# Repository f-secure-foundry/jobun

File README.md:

Introduction
============

jobun | https://github.com/f-secure-foundry/jobun  
Copyright (c) F-Secure Corporation

The jobun (序文) board implements a platform for transmission of truly
arbitrary Ethernet (802.3u - 100BASE-FX, 100BASETX and 10BASE-Te) packets, by
means of an FPGA based software Media Access Control (MAC) connected to a
physical (PHY) Ethernet transceiver.

The FPGA is a Lattice Semiconductor MachXO2 (P/N LCMXO2-1200HC-4SG32C), the
Ethernet transceiver is a Texas Instruments DP83822.

The PCB features a design that allows to use the FPGA side of the board
independently of the Ethernet PHY one. A 2.54mm 20x2 pin header must be
soldered to interconnect the two sides through connection shunts (jumpers).

With some courage, the two sides can also be snapped off each other for fully
independent use.

The board features a USB micro-AB receptacle for programming and operation.

The jobun design has been initially designed to provide a platform for the
Start-of-Frame delimiter (SFD) manipulation attacks described in the following
research:

* A. Barisani and D. Bianco
  “Fully Arbitrary 802.3 Packet Injection: Maximizing the Ethernet Attack Surface”  
  [Link](https://github.com/abarisani/abarisani.github.io/tree/master/research/802.3)

Authors
=======

Andrea Barisani  
andrea@inversepath.com  

Andrej Rosano  
andrej@inversepath.com  

Firmware
========

The on-board MachXO2 FPGA can be programmed, over USB, by placing a jumper on
the JP1 connector located on the upper left corner. The jumper must be then
removed and the board restarted to allow Ethernet PHY reconfiguration and
firmware startup.

The `firmware` directory contains a Lattice Diamond project file for a basic
packet transmission tool named file2cable to honour FX's homonym tool, part of
the legendary IRPAS from Phenoelit.

While the original IRPAS file2cable tool can be used to transmit a "MAC Frame",
jobun can send a "MAC Packet" (see paper linked earlier), therefore achieving
better coverage ;) in transmitting an actual file to the cable. The file in
question is `firmware/mac_pkt.txt`.

This [wiki](https://wiki.archlinux.org/index.php/Lattice_Diamond) contains
useful information on how to get started with Lattice Diamond.

Revision information
====================

Current schematics and layout files have been designed in KiCad 5.0.1.

PCB information
===============

2 layers, 1.60mm thickness, top only components  
Outer layers 0.5 oz base copper foil  
Inner layers   1 oz base copper foil  
width (X) 55.1 mm, height (Y) 50.5 mm  
Blue soldermask, white component legend

DRC information
---------------

Minimum track width:            0.254 mm  
Minimum via diameter:           0.450 mm  
Outer layer track width:        0.139 mm  
Outer layer isolation distance: 0.127 mm  
Outer layer annular ring:       0.100 mm  
Smallest final hole (plated):   0.150 mm

License
=======

Copyright (c) F-Secure Corporation

This is an open hardware design licensed under the terms of the CERN Open
Hardware Licence (OHL) v1.2.

You may redistribute and modify this documentation under the terms of the CERN
OHL v.1.2 (http://ohwr.org/cernohl). This documentation is distributed WITHOUT
ANY EXPRESS OR IMPLIED WARRANTY, INCLUDING OF MERCHANTABILITY, SATISFACTORY
QUALITY AND FITNESS FOR A PARTICULAR PURPOSE. Please see the CERN OHL v.1.2 for
applicable conditions.

The following exceptions apply:

- `hardware/lib.snapeda`: all files in this directory are imported or modified
  from SnapEDA symbols and footprints, therefore the license at
  https://www.snapeda.com/about/FAQ/#license applies.

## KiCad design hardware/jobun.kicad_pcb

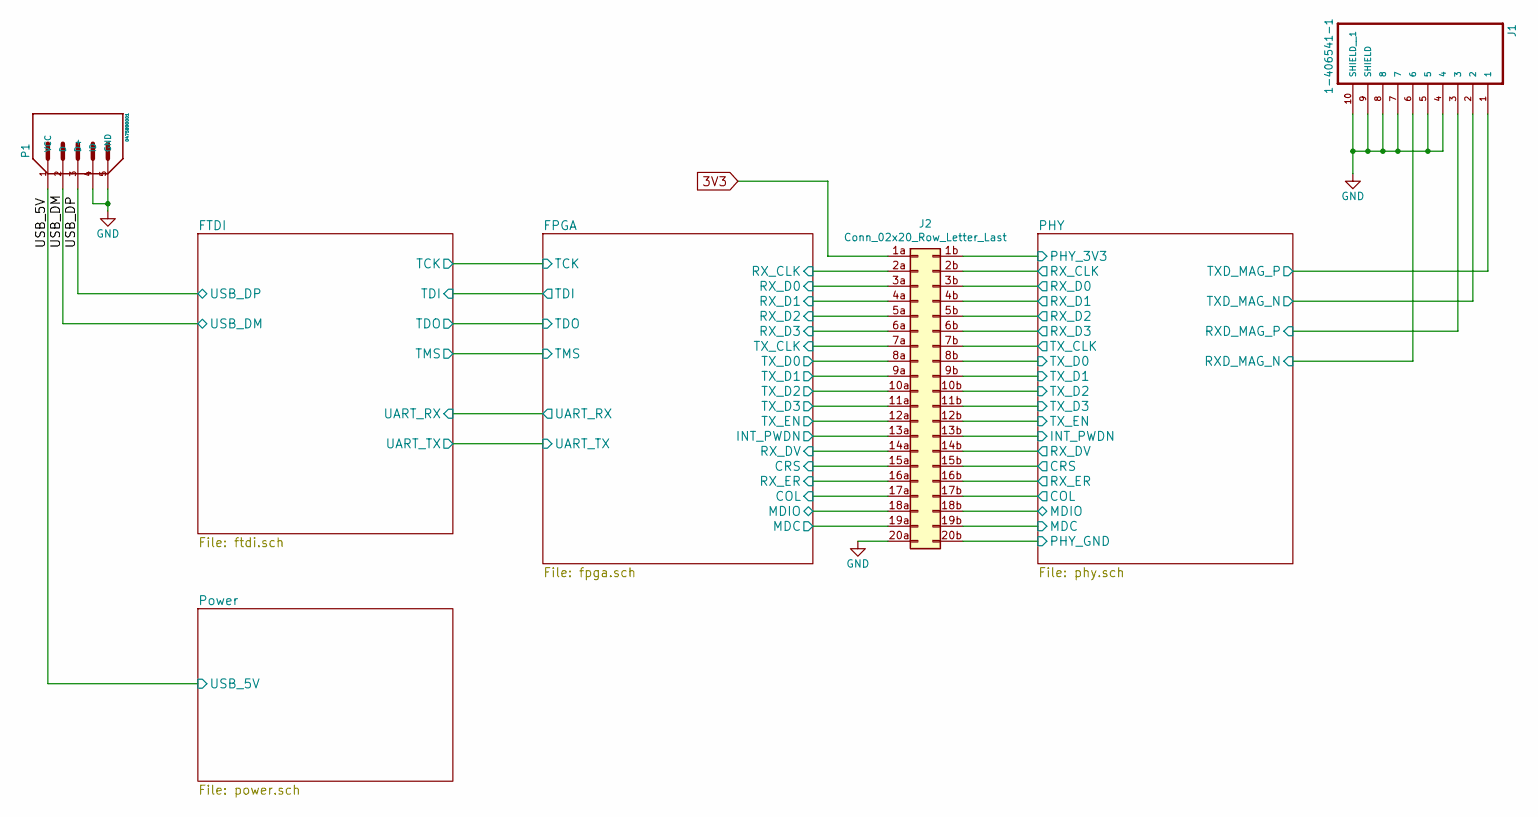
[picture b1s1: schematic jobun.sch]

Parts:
J1: 1-406541-1; CONN_1-406541-1; Mfg PN 1-406541-1
J2: Conn_02x20_Row_Letter_Last; jobun_pcb_mezzanine-20X2
P1: 0475890001; MOLEX_0475890001; Mfg PN 0475890001

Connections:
3V3: J2.1a; also elsewhere on the board
/FPGA/COL: J2.17a; also elsewhere on the board
/FPGA/CRS: J2.15a; also elsewhere on the board
/FPGA/INT_PWDN: J2.13a; also elsewhere on the board
/FPGA/MDC: J2.19a; also elsewhere on the board
/FPGA/MDIO: J2.18a; also elsewhere on the board
/FPGA/RX_CLK: J2.2a; also elsewhere on the board
/FPGA/RX_D0: J2.3a; also elsewhere on the board
/FPGA/RX_D1: J2.4a; also elsewhere on the board
/FPGA/RX_D2: J2.5a; also elsewhere on the board
/FPGA/RX_D3: J2.6a; also elsewhere on the board
/FPGA/RX_DV: J2.14a; also elsewhere on the board
/FPGA/RX_ER: J2.16a; also elsewhere on the board
/FPGA/TX_CLK: J2.7a; also elsewhere on the board
/FPGA/TX_D0: J2.8a; also elsewhere on the board
/FPGA/TX_D1: J2.9a; also elsewhere on the board
/FPGA/TX_D2: J2.10a; also elsewhere on the board
/FPGA/TX_D3: J2.11a; also elsewhere on the board
/FPGA/TX_EN: J2.12a; also elsewhere on the board
/PHY/COL: J2.17b; also elsewhere on the board
/PHY/CRS: J2.15b; also elsewhere on the board
/PHY/INT_PWDN: J2.13b; also elsewhere on the board
/PHY/MDC: J2.19b; also elsewhere on the board
/PHY/MDIO: J2.18b; also elsewhere on the board
/PHY/PHY_3V3: J2.1b; also elsewhere on the board
/PHY/RXD_MAG_N: J1.6; also elsewhere on the board
/PHY/RXD_MAG_P: J1.3; also elsewhere on the board
/PHY/RX_CLK: J2.2b; also elsewhere on the board
/PHY/RX_D0: J2.3b; also elsewhere on the board
/PHY/RX_D1: J2.4b; also elsewhere on the board
/PHY/RX_D2: J2.5b; also elsewhere on the board
/PHY/RX_D3: J2.6b; also elsewhere on the board
/PHY/RX_DV: J2.14b; also elsewhere on the board
/PHY/RX_ER: J2.16b; also elsewhere on the board
/PHY/TXD_MAG_N: J1.2; also elsewhere on the board
/PHY/TXD_MAG_P: J1.1; also elsewhere on the board
/PHY/TX_CLK: J2.7b; also elsewhere on the board
/PHY/TX_D0: J2.8b; also elsewhere on the board
/PHY/TX_D1: J2.9b; also elsewhere on the board
/PHY/TX_D2: J2.10b; also elsewhere on the board
/PHY/TX_D3: J2.11b; also elsewhere on the board
/PHY/TX_EN: J2.12b; also elsewhere on the board
/USB_5V: P1.1 (VCC); also elsewhere on the board
/USB_DM: P1.2 (D); also elsewhere on the board
/USB_DP: P1.3 (D+); also elsewhere on the board
GND: J1.4, J1.5, J1.7, J1.8, J1.9 (SHIELD), J1.10 (SHIELD__1), J2.20a, J2.20b, P1.4 (ID), P1.5 (GND); also elsewhere on the board

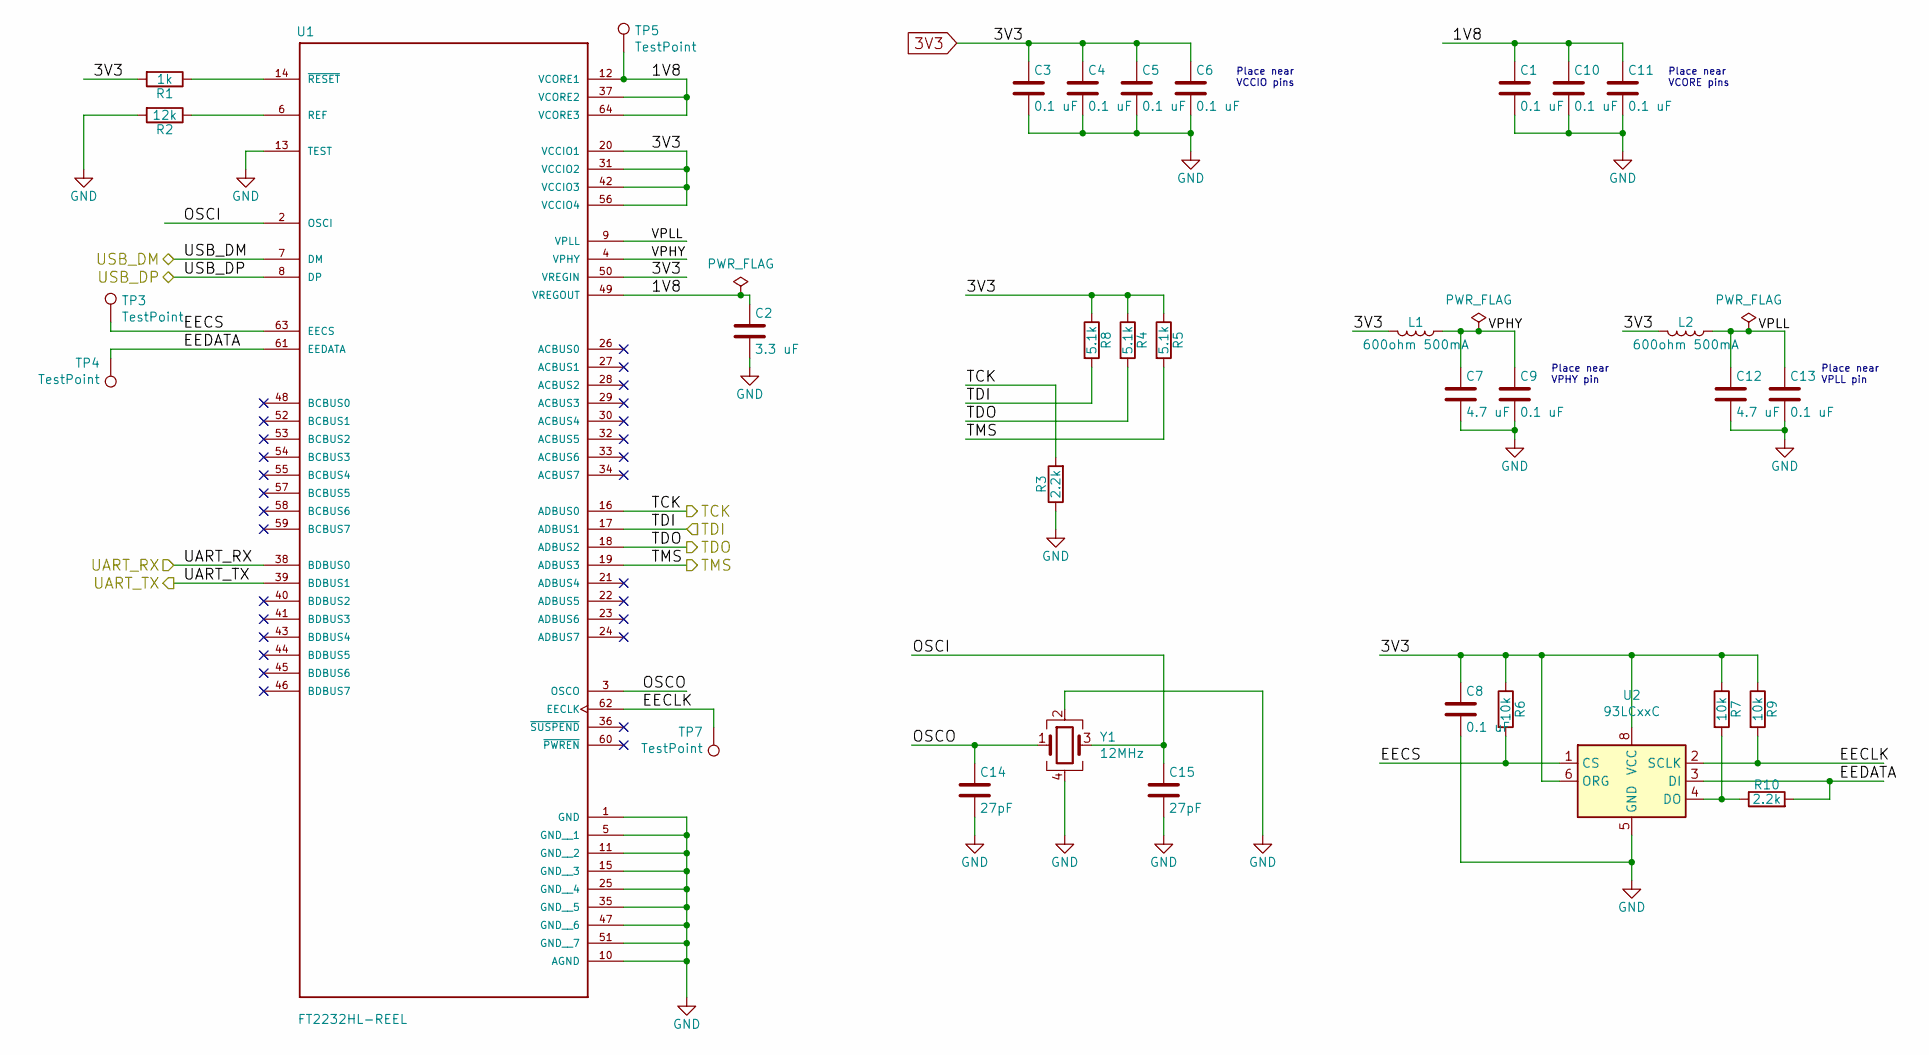
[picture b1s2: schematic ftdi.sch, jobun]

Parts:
C1, C3, C4, C5, C6, C8, C9, C10, C11, C13: 0.1 uF; SM0603; Mfg PN C1608X7R1E104K080AA
C2: 3.3 uF; SM0603; Mfg PN C1608X5R1C335K080AC
C7, C12: 4.7 uF; SM0603; Mfg PN CGB3B1X5R1A475M055AC
C14, C15: 27pF; SM0603; Mfg PN GRM1885C1H270FA01D
L1, L2: 600ohm 500mA; SM0603; Mfg PN BLM18AG601SN1D
R1: 1k; SM0603; Mfg PN RCA06031K00FKEAHP
R2: 12k; SM0603; Mfg PN CRCW060312K0FKEAC
R3, R10: 2.2k; SM0603; Mfg PN RCS06032K20JNEA
R4, R5, R8: 5.1k; SM0603; Mfg PN CRCW06035K10FKEAC
R6, R7, R9: 10k; SM0603; Mfg PN CRCW060310K0FKEA
TP3, TP4, TP5, TP7: TestPoint; TP
U1: FT2232HL-REEL; QFP50P1200X1200X160-64N; Mfg PN FT2232HL-REEL
U2: 93LCxxC; 8L_SOIC_Narrow_3_90_SN_C04-057C; Mfg PN 93LC56C-I/SN
Y1: 12MHz; TXC-3.2x2.5; Mfg PN 7M-12.000MAAJ-T

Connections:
3V3: C3.1, C4.1, C5.1, C6.1, C8.1, L1.1, L2.1, R1.2, R4.1, R5.1, R6.1, R7.1, R8.1, R9.1, U1.20 (VCCIO1), U1.31 (VCCIO2), U1.42 (VCCIO3), U1.50 (VREGIN), U1.56 (VCCIO4), U2.6 (ORG), U2.8 (VCC); also elsewhere on the board
/FPGA/TCK: R3.2, U1.16 (ADBUS0); also elsewhere on the board
/FPGA/TDI: R8.2, U1.17 (ADBUS1); also elsewhere on the board
/FPGA/TDO: R4.2, U1.18 (ADBUS2); also elsewhere on the board
/FPGA/TMS: R5.2, U1.19 (ADBUS3); also elsewhere on the board
/FPGA/UART_RX: U1.38 (BDBUS0); also elsewhere on the board
/FPGA/UART_TX: U1.39 (BDBUS1); also elsewhere on the board
/FTDI/1V8: C1.1, C2.1, C10.1, C11.1, TP5.1, U1.12 (VCORE1), U1.37 (VCORE2), U1.49 (VREGOUT), U1.64 (VCORE3)
/FTDI/EECLK: R9.2, TP7.1, U1.62 (EECLK), U2.2 (SCLK)
/FTDI/EECS: R6.2, TP3.1, U1.63 (EECS), U2.1 (CS)
/FTDI/EEDATA: R10.2, TP4.1, U1.61 (EEDATA), U2.3 (DI)
/FTDI/OSCI: C15.1, U1.2 (OSCI), Y1.3
/FTDI/OSCO: C14.1, U1.3 (OSCO), Y1.1
/FTDI/VPHY: C7.1, C9.1, L1.2, U1.4 (VPHY)
/FTDI/VPLL: C12.1, C13.1, L2.2, U1.9 (VPLL)
/USB_DM: U1.7 (DM); also elsewhere on the board
/USB_DP: U1.8 (DP); also elsewhere on the board
GND: C1.2, C2.2, C3.2, C4.2, C5.2, C6.2, C7.2, C8.2, C9.2, C10.2, C11.2, C12.2, C13.2, C14.2, C15.2, R2.2, R3.1, U1.1 (GND), U1.5 (GND__1), U1.10 (AGND), U1.11 (GND__2), U1.13 (TEST), U1.15 (GND__3), U1.25 (GND__4), U1.35 (GND__5), U1.47 (GND__6), U1.51 (GND__7), U2.5 (GND), Y1.2, Y1.4; also elsewhere on the board
unnamed: R1.1, U1.14 (~RESET~)
unnamed: R2.1, U1.6 (REF)
unnamed: R7.2, R10.1, U2.4 (DO)

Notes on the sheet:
Place near VCORE pins
Place near VCCIO pins
Place near VPLL pin
Place near VPHY pin

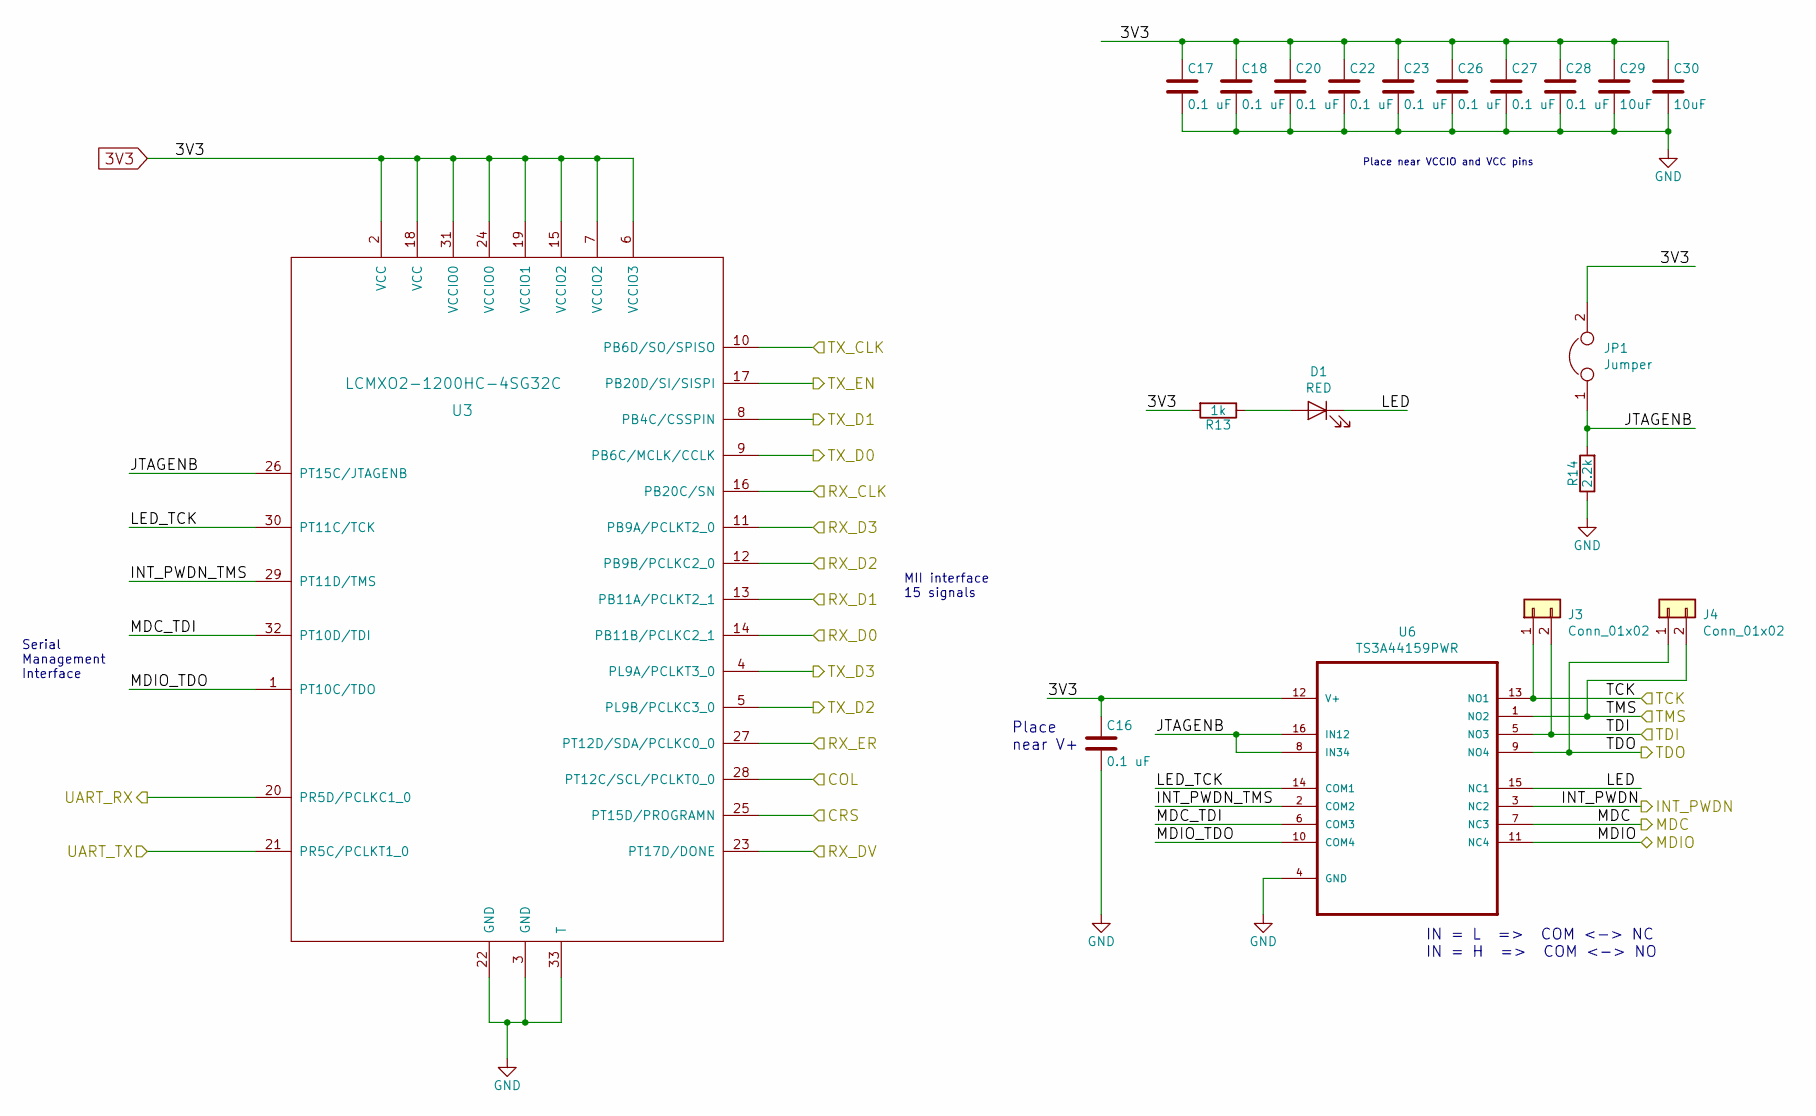
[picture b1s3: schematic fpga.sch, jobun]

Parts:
C16, C17, C18, C20, C22, C23, C26, C27, C28: 0.1 uF; SM0603; Mfg PN C1608X7R1E104K080AA
C29, C30: 10uF; SM0603; Mfg PN C1608X5R1A106M080AC
D1: RED; SM0603; Mfg PN LTST-C190KRKT
J3, J4: Conn_01x02; pinhead-1X2
JP1: Jumper; pinhead-1X2
R13: 1k; SM0603; Mfg PN RCA06031K00FKEAHP
R14: 2.2k; SM0603; Mfg PN RCS06032K20JNEA
U3: LCMXO2-1200HC-4SG32C; SG32C; Mfg PN LCMXO2-1200HC-4SG32C
U6: TS3A44159PWR; Mfg PN TS3A44159PWR

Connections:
3V3: C16.1, C17.1, C18.1, C20.1, C22.1, C23.1, C26.1, C27.1, C28.1, C29.1, C30.1, JP1.2, R13.2, U3.2 (VCC), U3.6 (VCCIO3), U3.7 (VCCIO2), U3.15 (VCCIO2), U3.18 (VCC), U3.19 (VCCIO1), U3.24 (VCCIO0), U3.31 (VCCIO0), U6.12 (V+); also elsewhere on the board
/FPGA/COL: U3.28 (PT12C/SCL/PCLKT0_0); also elsewhere on the board
/FPGA/CRS: U3.25 (PT15D/PROGRAMN); also elsewhere on the board
/FPGA/INT_PWDN: U6.3 (NC2); also elsewhere on the board
/FPGA/INT_PWDN_TMS: U3.29 (PT11D/TMS), U6.2 (COM2)
/FPGA/JTAGENB: JP1.1, R14.2, U3.26 (PT15C/JTAGENB), U6.8 (IN34), U6.16 (IN12)
/FPGA/LED: D1.1 (K), U6.15 (NC1)
/FPGA/LED_TCK: U3.30 (PT11C/TCK), U6.14 (COM1)
/FPGA/MDC: U6.7 (NC3); also elsewhere on the board
/FPGA/MDC_TDI: U3.32 (PT10D/TDI), U6.6 (COM3)
/FPGA/MDIO: U6.11 (NC4); also elsewhere on the board
/FPGA/MDIO_TDO: U3.1 (PT10C/TDO), U6.10 (COM4)
/FPGA/RX_CLK: U3.16 (PB20C/SN); also elsewhere on the board
/FPGA/RX_D0: U3.14 (PB11B/PCLKC2_1); also elsewhere on the board
/FPGA/RX_D1: U3.13 (PB11A/PCLKT2_1); also elsewhere on the board
/FPGA/RX_D2: U3.12 (PB9B/PCLKC2_0); also elsewhere on the board
/FPGA/RX_D3: U3.11 (PB9A/PCLKT2_0); also elsewhere on the board
/FPGA/RX_DV: U3.23 (PT17D/DONE); also elsewhere on the board
/FPGA/RX_ER: U3.27 (PT12D/SDA/PCLKC0_0); also elsewhere on the board
/FPGA/TCK: J3.1, U6.13 (NO1); also elsewhere on the board
/FPGA/TDI: J3.2, U6.5 (NO3); also elsewhere on the board
/FPGA/TDO: J4.1, U6.9 (NO4); also elsewhere on the board
/FPGA/TMS: J4.2, U6.1 (NO2); also elsewhere on the board
/FPGA/TX_CLK: U3.10 (PB6D/SO/SPISO); also elsewhere on the board
/FPGA/TX_D0: U3.9 (PB6C/MCLK/CCLK); also elsewhere on the board
/FPGA/TX_D1: U3.8 (PB4C/CSSPIN); also elsewhere on the board
/FPGA/TX_D2: U3.5 (PL9B/PCLKC3_0); also elsewhere on the board
/FPGA/TX_D3: U3.4 (PL9A/PCLKT3_0); also elsewhere on the board
/FPGA/TX_EN: U3.17 (PB20D/SI/SISPI); also elsewhere on the board
/FPGA/UART_RX: U3.20 (PR5D/PCLKC1_0); also elsewhere on the board
/FPGA/UART_TX: U3.21 (PR5C/PCLKT1_0); also elsewhere on the board
GND: C16.2, C17.2, C18.2, C20.2, C22.2, C23.2, C26.2, C27.2, C28.2, C29.2, C30.2, R14.1, U3.3 (GND), U3.22 (GND), U3.33 (T), U6.4 (GND); also elsewhere on the board
unnamed: D1.2 (A), R13.1

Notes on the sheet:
Place near VCCIO and VCC pins
MII interface 15 signals
Serial Management Interface
IN = L => COM <-> NC IN = H => COM <-> NO
Place near V+

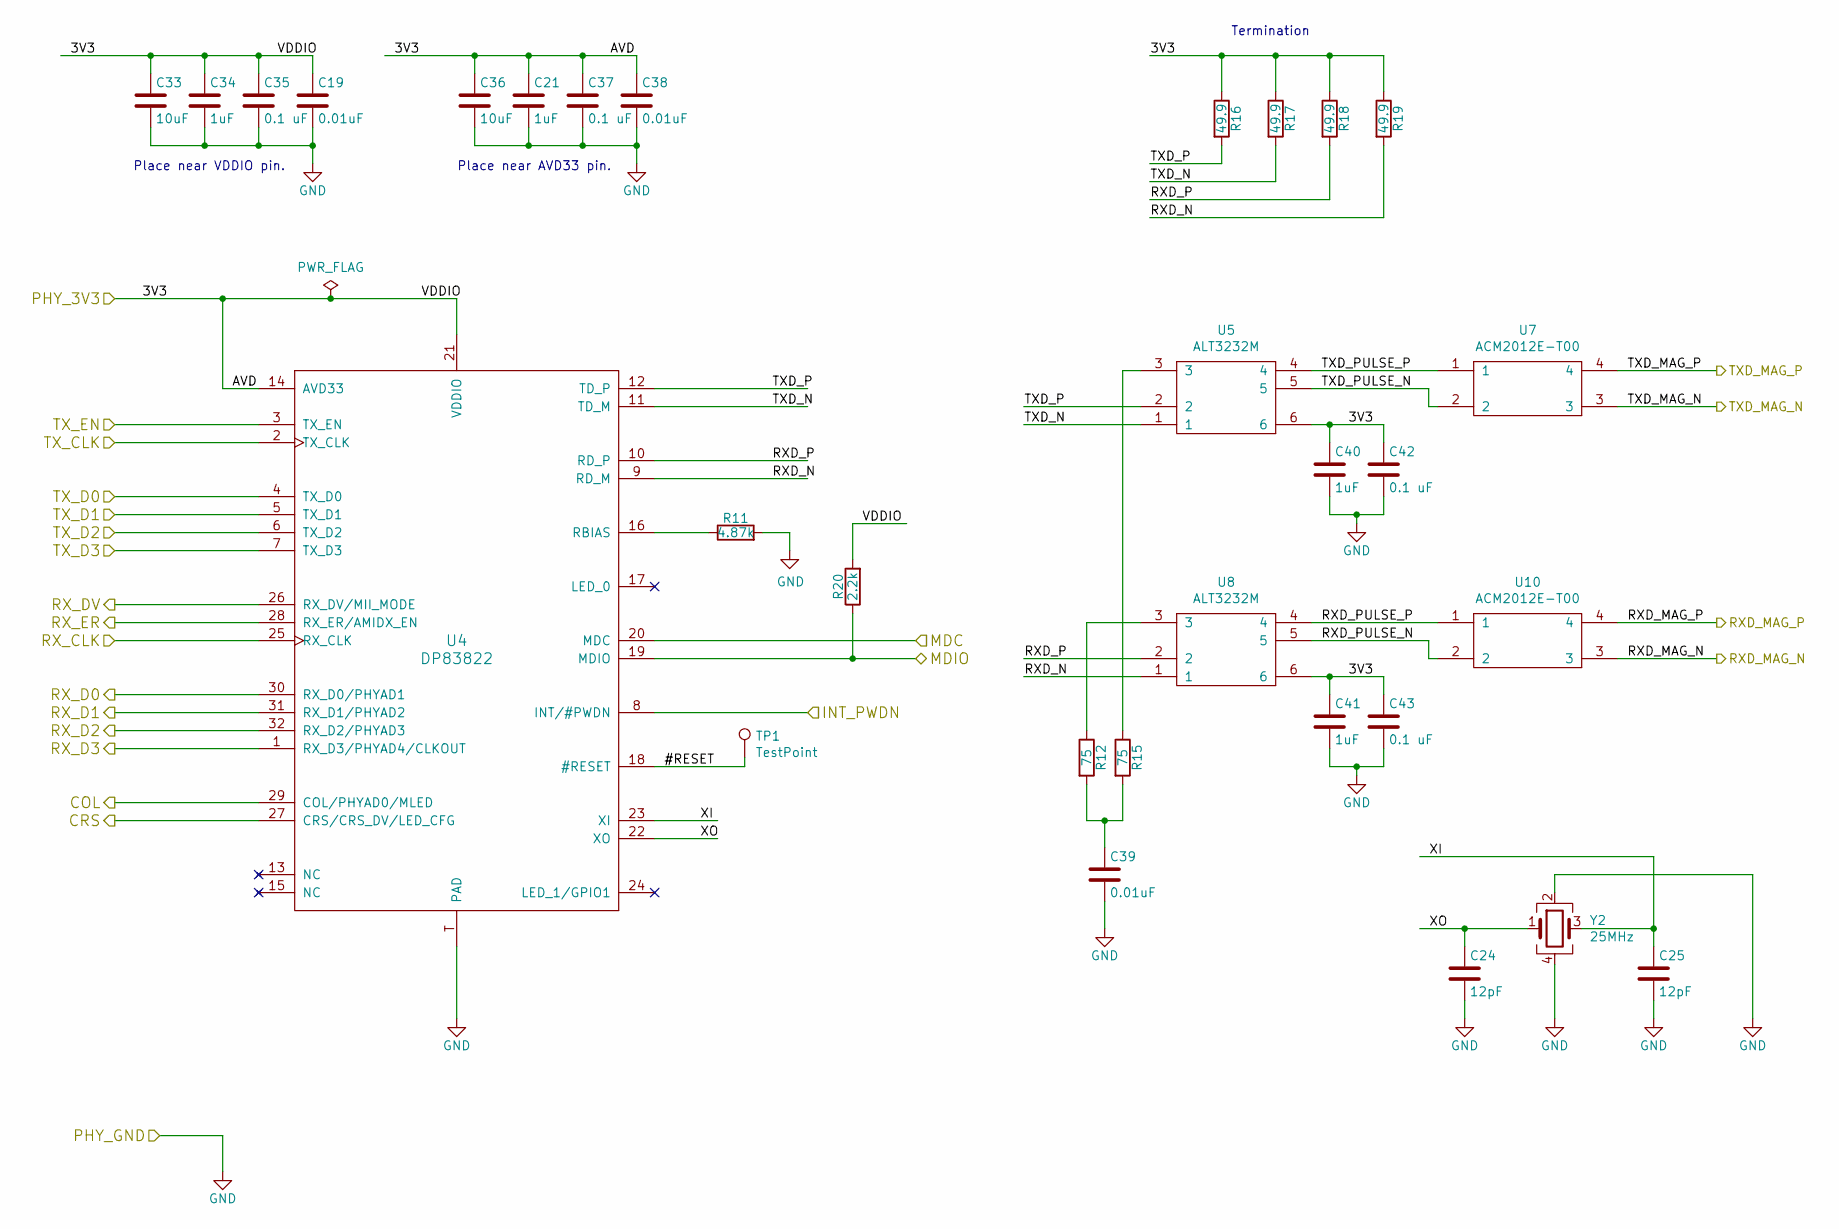
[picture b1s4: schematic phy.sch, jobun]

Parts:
C19, C38, C39: 0.01uF; SM0603; Mfg PN CGA3E2X7R2A103K080AA
C21, C34, C40, C41: 1uF; SM0603; Mfg PN CGA3E1X7R1C105M080AC
C24, C25: 12pF; SM0603; Mfg PN C1608NP02A120J080AA
C33, C36: 10uF; SM0603; Mfg PN C1608X5R1A106M080AC
C35, C37, C42, C43: 0.1 uF; SM0603; Mfg PN C1608X7R1E104K080AA
R11: 4.87k; SM0603; Mfg PN CRCW06034K87FKEA
R12, R15: 75; SM0603; Mfg PN RCS060375R0FKEA
R16, R17, R18, R19: 49.9; SM0603; Mfg PN CRCW060349R9FKEAHP
R20: 2.2k; SM0603; Mfg PN RCS06032K20JNEA
TP1: TestPoint; TP
U4: DP83822; VQFN-32; Mfg PN DP83822IFRHBT
U5, U8: ALT3232M; Mfg PN ALT3232M-151-T001
U7, U10: ACM2012E-T00; Mfg PN ACM2012E-900-2P-T00
Y2: 25MHz; OSCCC250X320X70-4N; Mfg PN ABM8AIG-25.000MHZ-12-2Z-T3

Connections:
/PHY/#RESET: TP1.1, U4.18 (#RESET)
/PHY/COL: U4.29 (COL/PHYAD0/MLED); also elsewhere on the board
/PHY/CRS: U4.27 (CRS/CRS_DV/LED_CFG); also elsewhere on the board
/PHY/INT_PWDN: U4.8 (INT/#PWDN); also elsewhere on the board
/PHY/MDC: U4.20 (MDC); also elsewhere on the board
/PHY/MDIO: R20.1, U4.19 (MDIO); also elsewhere on the board
/PHY/PHY_3V3: C19.1, C21.1, C33.1, C34.1, C35.1, C36.1, C37.1, C38.1, C40.1, C41.1, C42.1, C43.1, R16.1, R17.1, R18.1, R19.1, R20.2, U4.14 (AVD33), U4.21 (VDDIO), U5.6, U8.6; also elsewhere on the board
/PHY/RXD_MAG_N: U10.3; also elsewhere on the board
/PHY/RXD_MAG_P: U10.4; also elsewhere on the board
/PHY/RXD_N: R19.2, U4.9 (RD_M), U8.1
/PHY/RXD_P: R18.2, U4.10 (RD_P), U8.2
/PHY/RXD_PULSE_N: U8.5, U10.2
/PHY/RXD_PULSE_P: U8.4, U10.1
/PHY/RX_CLK: U4.25 (RX_CLK); also elsewhere on the board
/PHY/RX_D0: U4.30 (RX_D0/PHYAD1); also elsewhere on the board
/PHY/RX_D1: U4.31 (RX_D1/PHYAD2); also elsewhere on the board
/PHY/RX_D2: U4.32 (RX_D2/PHYAD3); also elsewhere on the board
/PHY/RX_D3: U4.1 (RX_D3/PHYAD4/CLKOUT); also elsewhere on the board
/PHY/RX_DV: U4.26 (RX_DV/MII_MODE); also elsewhere on the board
/PHY/RX_ER: U4.28 (RX_ER/AMIDX_EN); also elsewhere on the board
/PHY/TXD_MAG_N: U7.3; also elsewhere on the board
/PHY/TXD_MAG_P: U7.4; also elsewhere on the board
/PHY/TXD_N: R17.2, U4.11 (TD_M), U5.1
/PHY/TXD_P: R16.2, U4.12 (TD_P), U5.2
/PHY/TXD_PULSE_N: U5.5, U7.2
/PHY/TXD_PULSE_P: U5.4, U7.1
/PHY/TX_CLK: U4.2 (TX_CLK); also elsewhere on the board
/PHY/TX_D0: U4.4 (TX_D0); also elsewhere on the board
/PHY/TX_D1: U4.5 (TX_D1); also elsewhere on the board
/PHY/TX_D2: U4.6 (TX_D2); also elsewhere on the board
/PHY/TX_D3: U4.7 (TX_D3); also elsewhere on the board
/PHY/TX_EN: U4.3 (TX_EN); also elsewhere on the board
/PHY/XI: C25.1, U4.23 (XI), Y2.3
/PHY/XO: C24.1, U4.22 (XO), Y2.1
GND: C19.2, C21.2, C24.2, C25.2, C33.2, C34.2, C35.2, C36.2, C37.2, C38.2, C39.2, C40.2, C41.2, C42.2, C43.2, R11.2, U4.T (PAD), Y2.2, Y2.4; also elsewhere on the board
unnamed: C39.1, R12.2, R15.2
unnamed: R11.1, U4.16 (RBIAS)
unnamed: R12.1, U8.3
unnamed: R15.1, U5.3

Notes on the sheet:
Termination
Place near AVD33 pin.
Place near VDDIO pin.

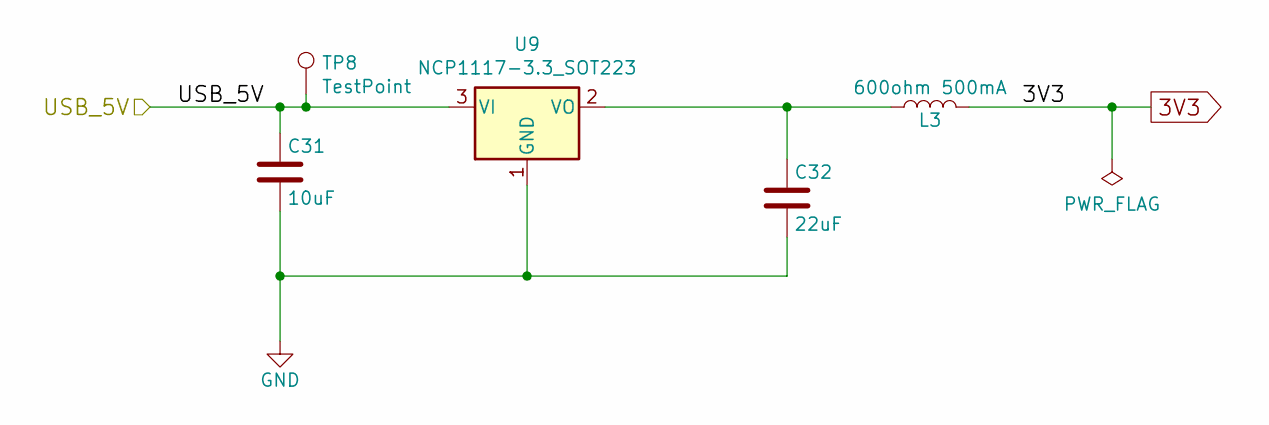
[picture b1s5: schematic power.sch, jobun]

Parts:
C31: 10uF; SM0603; Mfg PN C1608X5R1A106M080AC
C32: 22uF; SM0603; Mfg PN C1608X5R1A226M080AC
L3: 600ohm 500mA; SM0603; Mfg PN BLM18AG601SN1D
TP8: TestPoint; TP
U9: NCP1117-3.3_SOT223; SOT-223; Mfg PN NCP1117ST33T3G

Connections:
3V3: L3.2; also elsewhere on the board
/USB_5V: C31.1, TP8.1, U9.3 (VI); also elsewhere on the board
GND: C31.2, C32.2, U9.1 (GND); also elsewhere on the board
unnamed: C32.1, L3.1, U9.2 (VO)

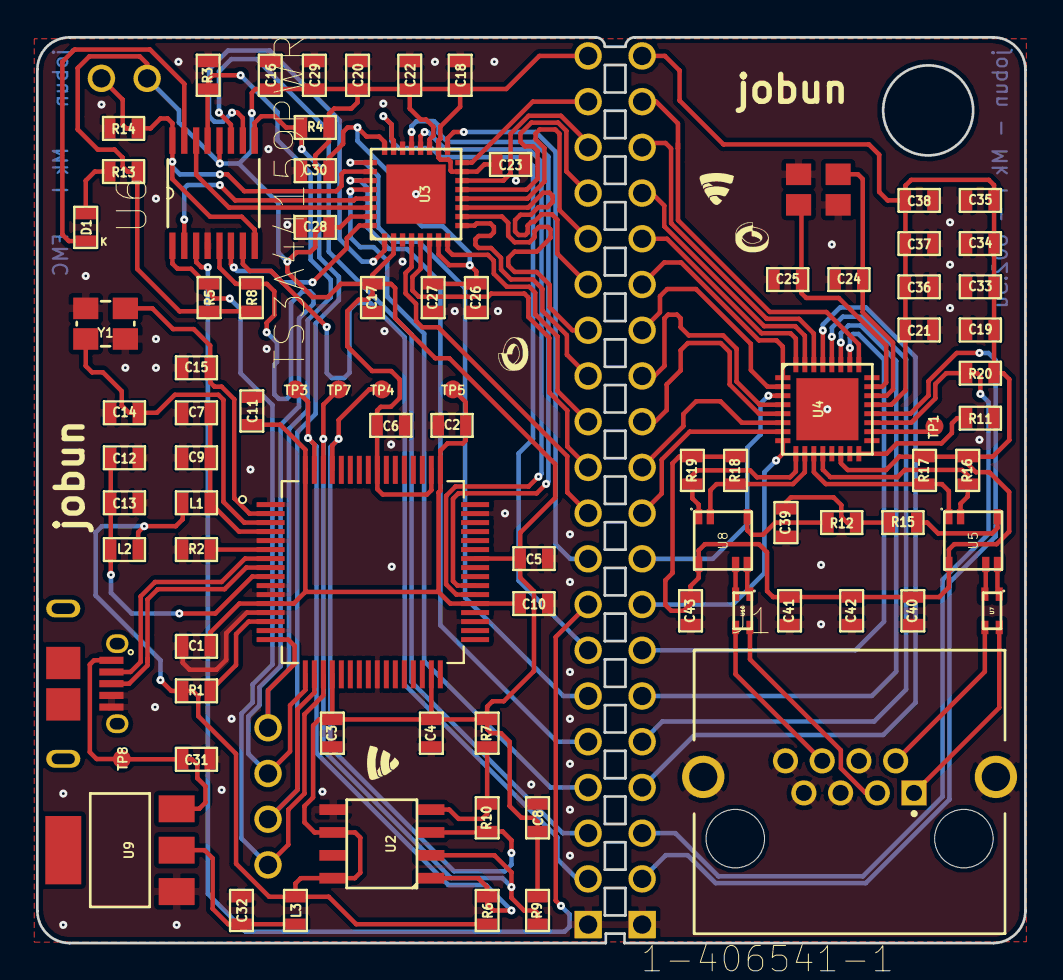
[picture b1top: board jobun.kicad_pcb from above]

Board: 2 copper layers, 54.9 x 50.3 mm, 95 parts (0 on the bottom side), 86 nets.

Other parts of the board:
FSC_LOGO_NO_TEXT_SMALL: G***; FSC_LOGO_NO_TEXT_SMALL
FSC_LOGO_NO_TEXT_SMALL#2: G***; FSC_LOGO_NO_TEXT_SMALL
Ref**: Val**; IP_LOGO_NO_TEXT_SMALL
Ref**#2: Val**; IP_LOGO_NO_TEXT_SMALL

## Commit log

2019-01-08 initial import
2019-01-08 link board image
2019-01-08 tidying
2019-01-08 highlight FPGA P/N
2019-01-09 code cleanup and set minimum inter-frame gap value
2019-01-10 highlight PHY P/N
2020-01-13 rename organization
2022-02-11 Remove broken link
2022-12-20 remove old email addresses

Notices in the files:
hardware/fpga.sch:
Copyright © F-Secure Corporation
License: CERN OHL v1.2
